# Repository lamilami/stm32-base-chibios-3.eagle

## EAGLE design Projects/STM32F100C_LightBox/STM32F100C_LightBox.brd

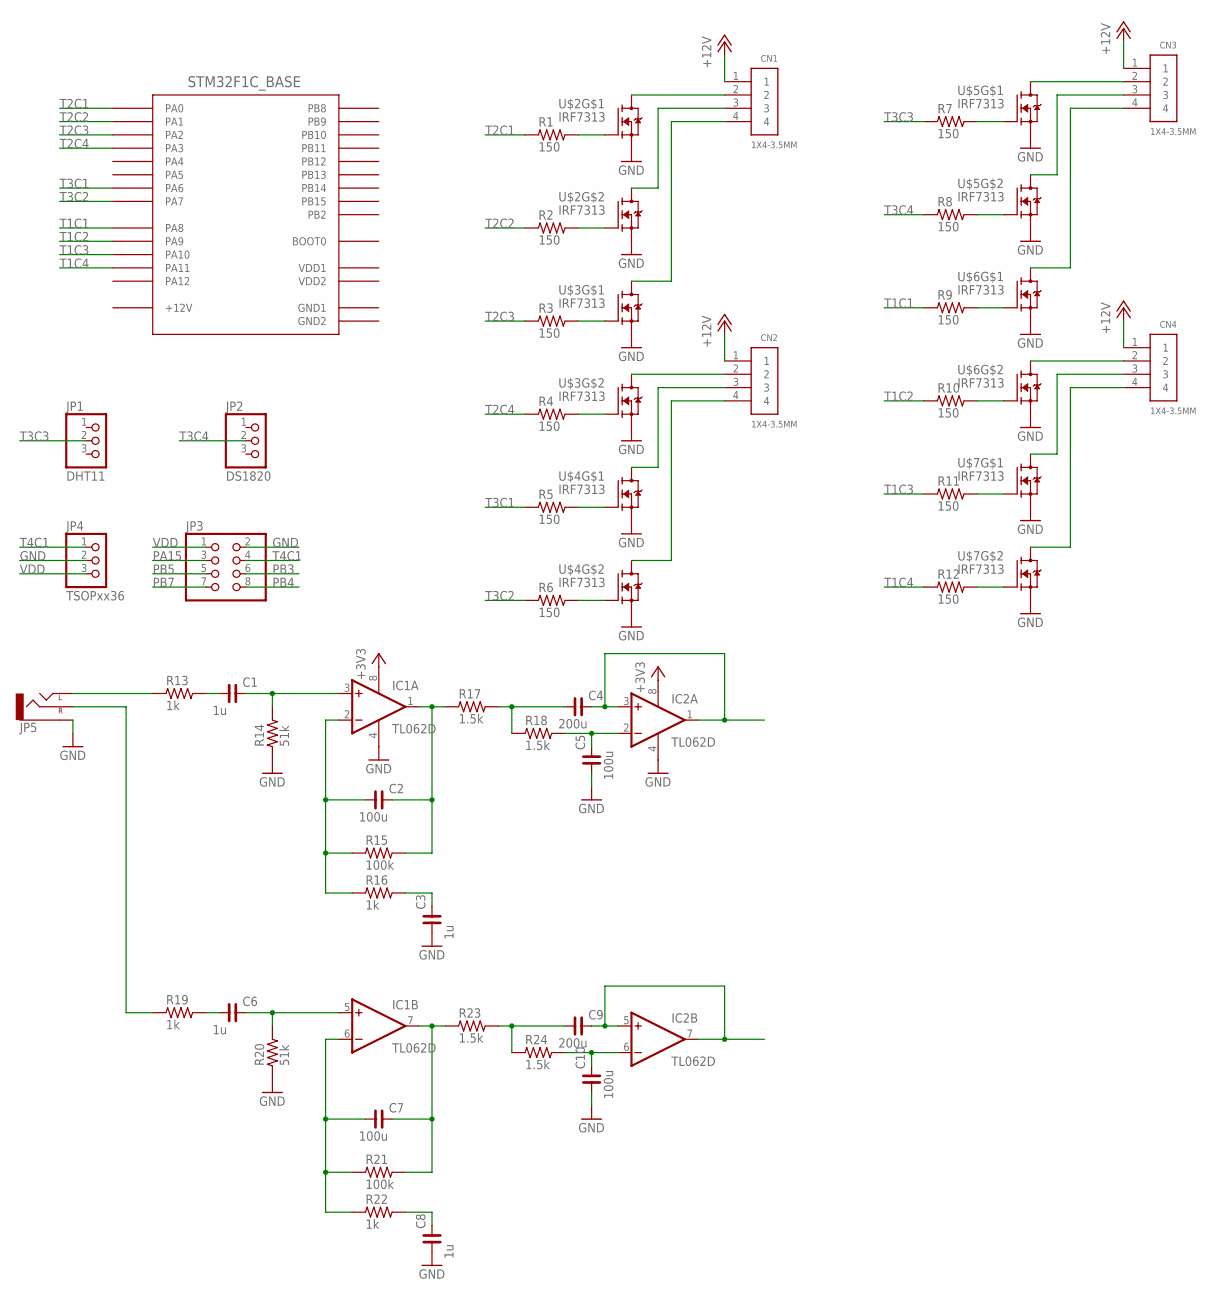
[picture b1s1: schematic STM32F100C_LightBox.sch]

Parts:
C1, C3, C6, C8: 1u; C0603
C2, C5, C7, C10: 100u; C0603
C4, C9: 200u; C0603
CN1, CN2, CN3, CN4: 1X4-3.5MM; 1X04-3.5MM
IC1, IC2: TL062D; SO08
JP1: DHT11; 1X03
JP2: DS1820; 1X03
JP3: PINHD-2X04_2.54; 2X04
JP4: TSOPxx36; 1X03
JP5: AUDIO-JACK; AUB-13
R1, R2, R3, R4, R5, R6, R7, R8, R9, R10, R11, R12: 150; R1206
R13, R16, R19, R22: 1k; R1206
R14, R20: 51k; R1206
R15, R21: 100k; R1206
R17, R18, R23, R24: 1.5k; R1206
U$1: STM32F1C_BASE; STM32F1_BASE
U$2, U$3, U$4, U$5, U$6, U$7: IRF7313; SO-8

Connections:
+3V3: IC1.8 (V+), IC2.8 (V+)
+12V: CN1.1, CN2.1, CN3.1, CN4.1, U$1.+12 (+12V)
GND: C3.1, C5.1, C8.1, C10.1, IC1.4 (V-), IC2.4 (V-), JP3.2, JP4.2, JP5.1 (SLEEVE), R14.1, R20.1, U$2.1 (S), U$2.3 (S), U$3.1 (S), U$3.3 (S), U$4.1 (S), U$4.3 (S), U$5.1 (S), U$5.3 (S), U$6.1 (S), U$6.3 (S), U$7.1 (S), U$7.3 (S)
unnamed: CN1.2, U$2.7 (D), U$2.8 (D)
unnamed: CN1.3, U$2.5 (D), U$2.6 (D)
unnamed: CN1.4, U$3.7 (D), U$3.8 (D)
unnamed: CN2.2, U$3.5 (D), U$3.6 (D)
unnamed: CN2.3, U$4.7 (D), U$4.8 (D)
unnamed: CN2.4, U$4.5 (D), U$4.6 (D)
unnamed: R1.2, U$2.2 (G)
unnamed: R2.2, U$2.4 (G)
unnamed: R3.2, U$3.2 (G)
unnamed: R4.2, U$3.4 (G)
unnamed: R5.2, U$4.2 (G)
unnamed: CN3.2, U$5.7 (D), U$5.8 (D)
unnamed: CN3.3, U$5.5 (D), U$5.6 (D)
unnamed: CN3.4, U$6.7 (D), U$6.8 (D)
unnamed: CN4.2, U$6.5 (D), U$6.6 (D)
unnamed: CN4.3, U$7.7 (D), U$7.8 (D)
unnamed: CN4.4, U$7.5 (D), U$7.6 (D)
unnamed: R7.2, U$5.2 (G)
unnamed: R8.2, U$5.4 (G)
unnamed: R9.2, U$6.2 (G)
unnamed: R10.2, U$6.4 (G)
unnamed: R11.2, U$7.2 (G)
unnamed: R6.2, U$4.4 (G)
unnamed: R12.2, U$7.4 (G)
unnamed: JP5.3 (LEFT), R13.1
unnamed: C1.1, R13.2
unnamed: C1.2, IC1.3 (+IN), R14.2
unnamed: C2.1, IC1.2 (-IN), R15.1, R16.1
unnamed: C2.2, IC1.1 (OUT), R15.2, R17.1
unnamed: C3.2, R16.2
unnamed: JP5.2 (RIGHT), R19.1
unnamed: C5.2, IC2.2 (-IN), R18.2
unnamed: C4.1, R17.2, R18.1
unnamed: C4.2, IC2.1 (OUT), IC2.3 (+IN)
unnamed: C6.1, R19.2
unnamed: C6.2, IC1.5 (+IN), R20.2
unnamed: C7.1, IC1.6 (-IN), R21.1, R22.1
unnamed: C7.2, IC1.7 (OUT), R21.2, R23.1
unnamed: C8.2, R22.2
unnamed: C9.1, R23.2, R24.1
unnamed: C10.2, IC2.6 (-IN), R24.2
unnamed: C9.2, IC2.5 (+IN), IC2.7 (OUT)
PA15: JP3.3
PB3: JP3.6
PB4: JP3.8
PB5: JP3.5
PB7: JP3.7
T1C1: R9.1, U$1.PA8
T1C2: R10.1, U$1.PA9
T1C3: R11.1, U$1.PA10
T1C4: R12.1, U$1.PA11
T2C1: R1.1, U$1.PA0
T2C2: R2.1, U$1.PA1
T2C3: R3.1, U$1.PA2
T2C4: R4.1, U$1.PA3
T3C1: R5.1, U$1.PA6
T3C2: R6.1, U$1.PA7
T3C3: JP1.2, R7.1
T3C4: JP2.2, R8.1
T4C1: JP3.4, JP4.1
VDD: JP3.1, JP4.3

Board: 2 copper layers, 52 parts (0 on the bottom side), 59 nets, no tracks yet.

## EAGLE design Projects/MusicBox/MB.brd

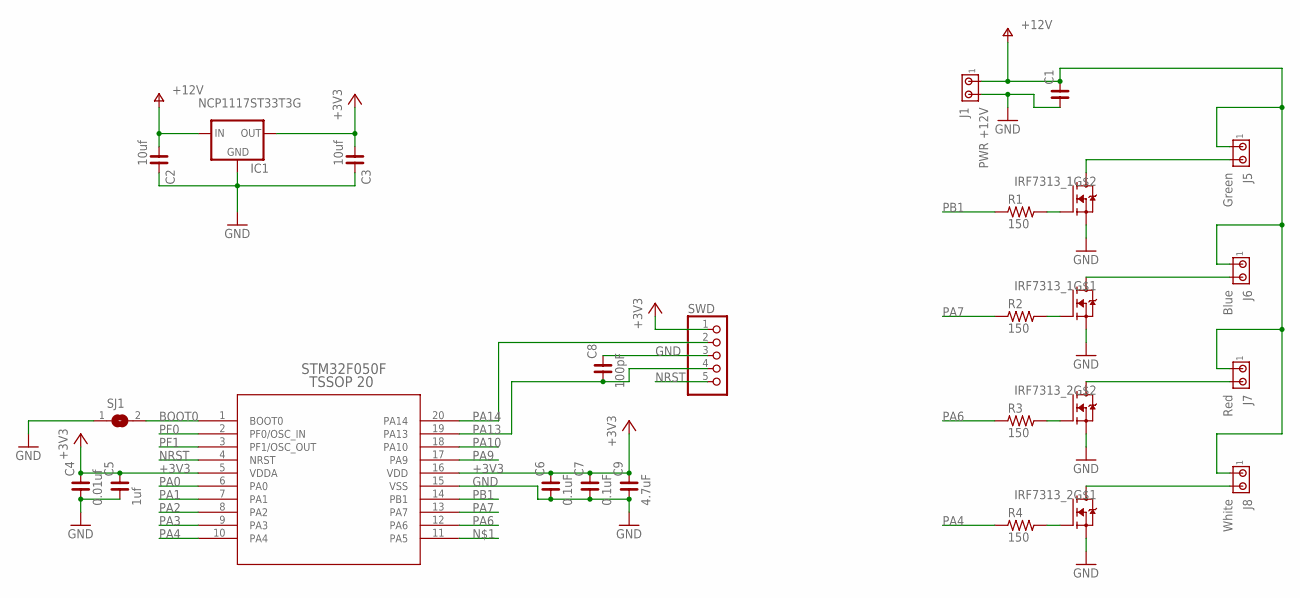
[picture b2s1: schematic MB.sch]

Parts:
C1: C_1206; C1206
C2, C3: 10uf; C1206
C4: 0.01uf; C1206
C5: 1uf; C1206
C6, C7: 0.1uF; C1206
C8: 100pF; C1206
C9: 4.7uF; C1206
IC1: NCP1117ST33T3G; SOT223
IRF7313_1, IRF7313_2: IRF7313; SO-8
J1: PWR +12V; 10X02MTA
J5: Green; 10X02MTA
J6: Blue; 10X02MTA
J7: Red; 10X02MTA
J8: White; 10X02MTA
R1, R2, R3, R4: 150; R1206
SJ1: SJ
SWD: PINHD-1X05_2.54-90°-S; 1X05/90-S
U$4: STM32F050F4P6; TSSOP20

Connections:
+3V3: C3.1, C4.2, C5.2, C6.2, C7.2, C9.2, IC1.2 (OUT), SWD.1, U$4.5 (VDDA), U$4.16 (VDD)
BOOT0: SJ1.2, U$4.1 (BOOT0)
GND: C1.1, C2.2, C3.2, C4.1, C5.1, C6.1, C7.1, C8.2, C9.1, IC1.1 (GND), IRF7313_1.1 (S), IRF7313_1.3 (S), IRF7313_2.1 (S), IRF7313_2.3 (S), J1.2, SJ1.1, SWD.3, U$4.15 (VSS)
unnamed: IRF7313_1.5 (D), IRF7313_1.6 (D), J5.2
unnamed: IRF7313_1.4 (G), R1.2
unnamed: IRF7313_1.2 (G), R2.2
unnamed: IRF7313_2.2 (G), R4.2
unnamed: IRF7313_2.4 (G), R3.2
unnamed: IRF7313_1.7 (D), IRF7313_1.8 (D), J6.2
unnamed: IRF7313_2.5 (D), IRF7313_2.6 (D), J7.2
unnamed: IRF7313_2.7 (D), IRF7313_2.8 (D), J8.2
NRST: SWD.5, U$4.4 (NRST)
PA0: U$4.6 (PA0)
PA1: U$4.7 (PA1)
PA2: U$4.8 (PA2)
PA3: U$4.9 (PA3)
PA4: R4.1, U$4.10 (PA4)
PA6: R3.1, U$4.12 (PA6)
PA7: R2.1, U$4.13 (PA7)
PA9: U$4.17 (PA9)
PA10: U$4.18 (PA10)
PA13: C8.1, SWD.4, U$4.19 (PA13)
PA14: SWD.2, U$4.20 (PA14)
PB1: R1.1, U$4.14 (PB1)
PF0: U$4.2 (PF0/OSC_IN)
PF1: U$4.3 (PF1/OSC_OUT)
V+: C1.2, C2.1, IC1.3 (IN), J1.1, J5.1, J6.1, J7.1, J8.1

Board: 2 copper layers, 24 parts (0 on the bottom side), 19 nets, no tracks yet.

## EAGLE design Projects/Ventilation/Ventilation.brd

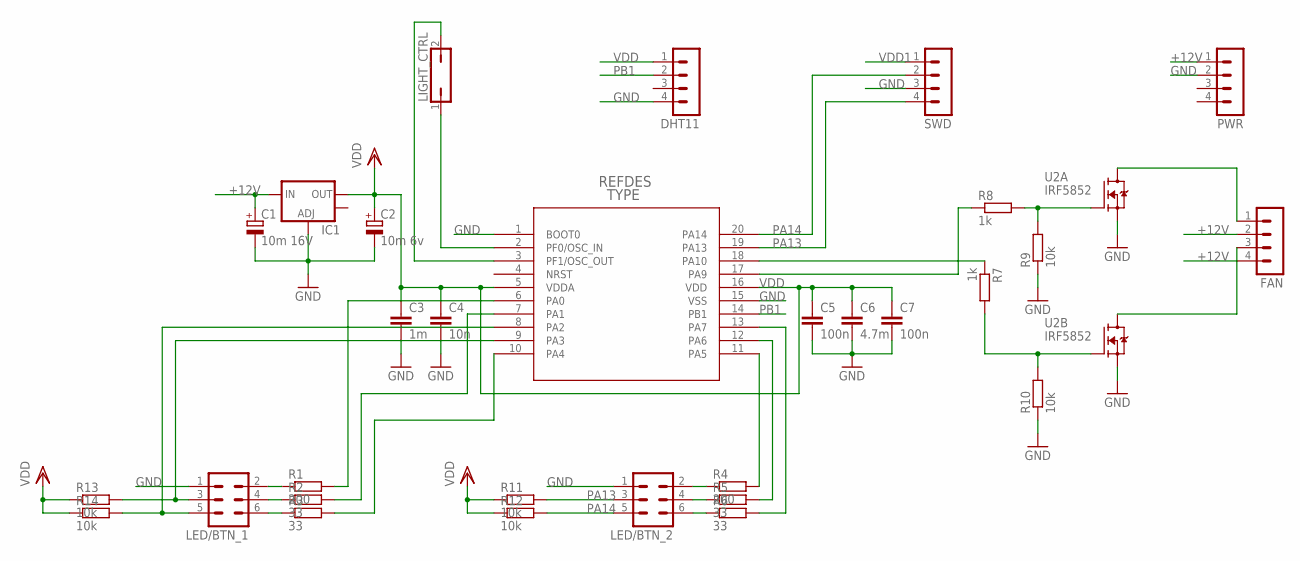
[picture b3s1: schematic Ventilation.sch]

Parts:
C1: 10m 16V; SMC_A
C2: 10m 6v; SMC_A
C3: 1m; C1206
C4: 10n; C1206
C5, C7: 100n; C1206
C6: 4.7m; C1206
DHT11: MA04-1
FAN: MA04-1
IC1: V_REG_LM1117SOT223; SOT223
LED/BTN_1, LED/BTN_2: MA03-2
LIGHT_CTRL: JP1Q; JP1
PWR: MA04-1
R1, R4: 200; R1206
R2, R3, R5, R6: 33; R1206
R7, R8: 1k; R1206
R9, R10, R11, R12, R13, R14: 10k; R1206
SWD: MA04-1
U2: IRF5852; SOT23-6
U$1: STM32F050F4P6; TSSOP20

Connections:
+12V: C1.+, FAN.2, FAN.4, IC1.3 (IN), PWR.1
GND: C1.-, C2.-, C3.2, C4.2, C5.2, C6.2, C7.2, DHT11.4, IC1.1 (ADJ), LED/BTN_1.1, LED/BTN_2.1, PWR.2, R9.1, R10.1, SWD.3, U2.2 (S), U2.5 (S), U$1.1 (BOOT0), U$1.15 (VSS)
unnamed: R8.1, U$1.17 (PA9)
unnamed: R7.2, R10.2, U2.3 (G)
unnamed: FAN.1, U2.6 (D)
unnamed: FAN.3, U2.4 (D)
unnamed: R7.1, U$1.18 (PA10)
unnamed: R8.2, R9.2, U2.1 (G)
unnamed: R1.2, U$1.6 (PA0)
unnamed: LIGHT_CTRL.1, U$1.2 (PF0/OSC_IN)
unnamed: LIGHT_CTRL.2, U$1.3 (PF1/OSC_OUT)
unnamed: R2.2, U$1.7 (PA1)
unnamed: LED/BTN_1.3, R13.2, U$1.9 (PA3)
unnamed: LED/BTN_1.5, R14.2, U$1.8 (PA2)
unnamed: LED/BTN_2.2, R4.1
unnamed: LED/BTN_2.4, R5.1
unnamed: LED/BTN_2.6, R6.1
unnamed: LED/BTN_1.2, R1.1
unnamed: LED/BTN_1.4, R2.1
unnamed: LED/BTN_1.6, R3.1
unnamed: R5.2, U$1.12 (PA6)
unnamed: R6.2, U$1.13 (PA7)
unnamed: R4.2, U$1.11 (PA5)
unnamed: R3.2, U$1.10 (PA4)
PA13: LED/BTN_2.3, R11.2, SWD.4, U$1.19 (PA13)
PA14: LED/BTN_2.5, R12.2, SWD.2, U$1.20 (PA14)
PB1: DHT11.2, U$1.14 (PB1)
VDD: C2.+, C3.1, C4.1, C5.1, C6.1, C7.1, DHT11.1, IC1.2 (OUT), R11.1, R12.1, R13.1, R14.1, U$1.5 (VDDA), U$1.16 (VDD)
VDD1: SWD.1

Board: 2 copper layers, 31 parts (0 on the bottom side), 28 nets, no tracks yet.

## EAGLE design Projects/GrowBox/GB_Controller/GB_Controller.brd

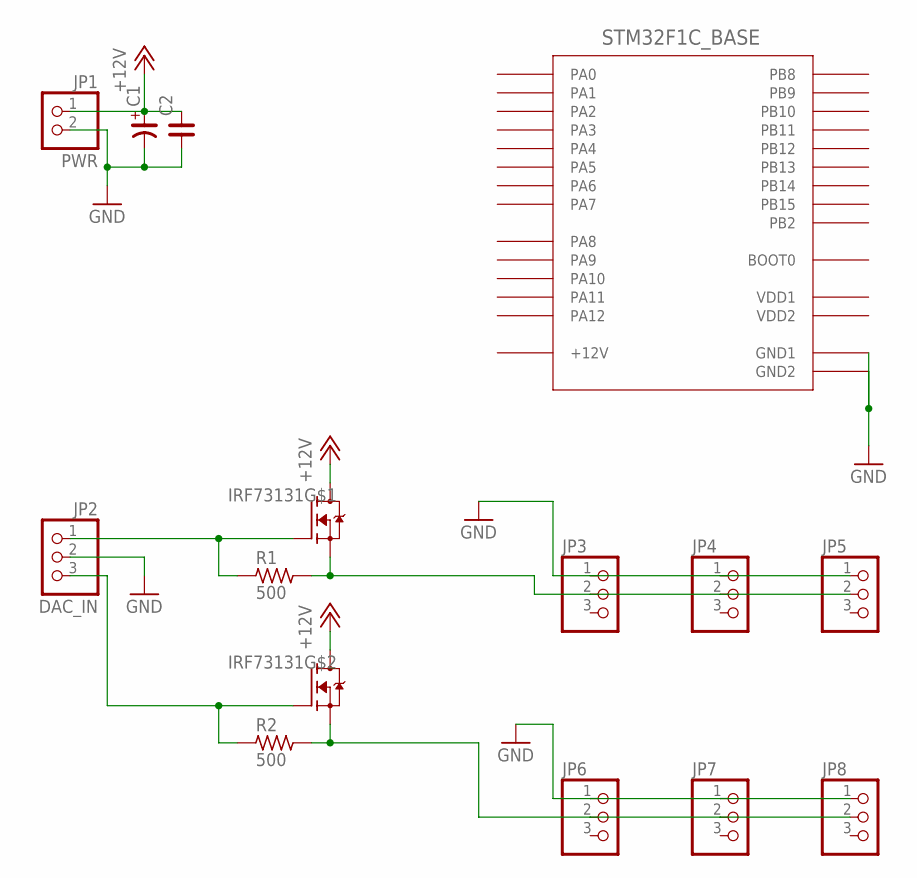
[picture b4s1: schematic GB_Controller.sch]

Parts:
C1: CP_7343; C7343/T
C2: C_0603; C0603
IRF73131: IRF7313; SO-8
JP1: PWR; 1X02-S
JP2: DAC_IN; 1X03-S
JP3, JP4, JP5, JP6, JP7, JP8: PINHD-1X03_2.54-S; 1X03-S
R1, R2: 500; R1206
STM32F1C_BASE1: STM32F1C_BASE; STM32F1_BASE

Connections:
+12V: C1.+, C2.2, IRF73131.5 (D), IRF73131.6 (D), IRF73131.7 (D), IRF73131.8 (D), JP1.1, STM32F1C_BASE1.+12 (+12V)
GND: C1.-, C2.1, JP1.2, JP2.2, JP3.1, JP4.1, JP5.1, JP6.1, JP7.1, JP8.1, STM32F1C_BASE1.GND (GND1), STM32F1C_BASE1.GND1 (GND2)
unnamed: IRF73131.1 (S), JP3.2, JP4.2, JP5.2, R1.2
unnamed: IRF73131.4 (G), JP2.3, R2.1
unnamed: IRF73131.2 (G), JP2.1, R1.1
unnamed: IRF73131.3 (S), JP6.2, JP7.2, JP8.2, R2.2

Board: 2 copper layers, 14 parts (0 on the bottom side), 6 nets, no tracks yet.

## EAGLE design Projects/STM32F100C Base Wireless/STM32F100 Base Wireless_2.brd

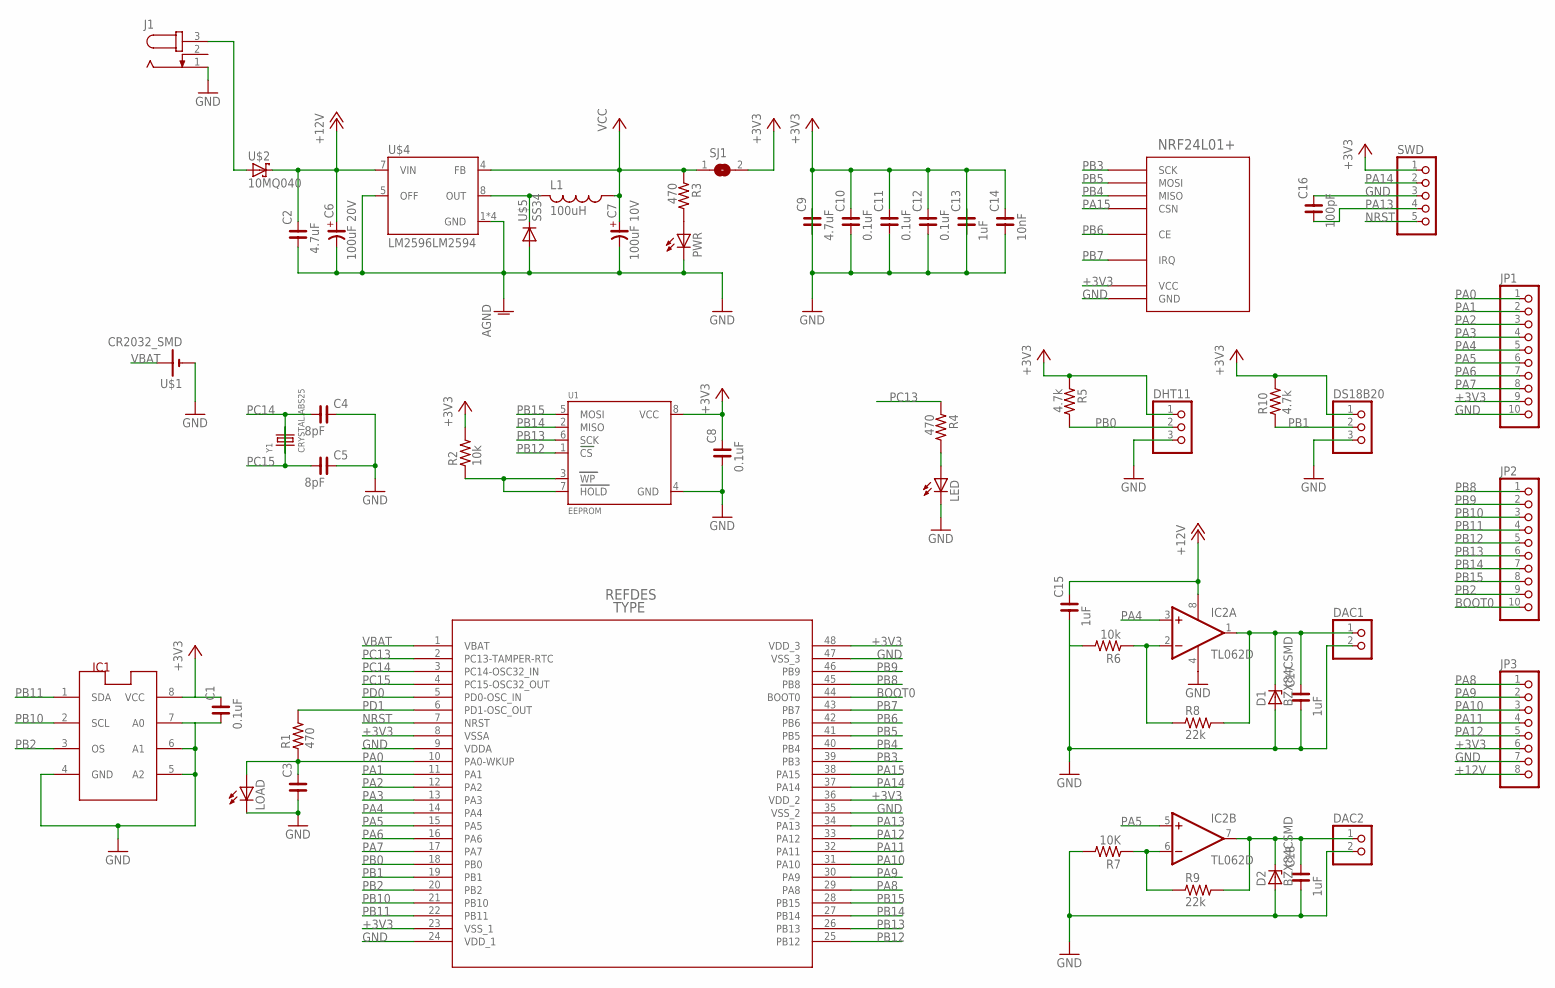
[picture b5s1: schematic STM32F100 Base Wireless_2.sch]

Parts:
C1, C8, C10, C11, C12: 0.1uF; C0603
C2, C9: 4.7uF; C0603
C3: C_0603; C0603
C4, C5: 8pF; C0603
C6: 100uF 20V; C7343/T
C7: 100uF 10V; C6032-28/T
C13, C15, C17, C18: 1uF; C0603
C14: 10nF; C0603
C16: 100pF; C0603
D1, D2: BZX84CSMD; TO236
DAC1, DAC2: PINHD-1X02_2.54-S; 1X02-S
DHT11: PINHD-1X03_2.54-S; 1X03-S
DS18B20: PINHD-1X03_2.54-S; 1X03-S
IC1: LM75_ICN; SO8_LM75
IC2: TL062D; SO08
J1: JACK-PLUG0; SPC4077
JP1, JP2: PINHD-1X10_2.54-S; 1X10-S
JP3: PINHD-1X08_2.54-S; 1X08-S
L1: 100uH; POWER-CHOKE_WE-TPC
LED: LEDCHIPLED_1206; CHIPLED_1206
LOAD: LEDCHIPLED_1206; CHIPLED_1206
PWR: LEDCHIPLED_1206; CHIPLED_1206
R1, R3, R4: 470; R1206
R2, R6: 10k; R1206
R5, R10: 4.7k; R1206
R7: 10K; R1206
R8, R9: 22k; R1206
SJ1: SJ
SWD: PINHD-1X05_2.54-90°-S; 1X05/90-S
U1: EEPROM; SOIC8_150MIL
U$1: CR2032_SMD; SMD_BH-2
U$2: 10MQ040; SMA
U$3: STM32F100C8T6B; LQFP-48
U$4: LM2596LM2594; SOIC8_150MIL
U$5: SS34; DO214AC
U$6: NRF24L01+
Y1: CRYSTAL.ABS25; ABS25

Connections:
+3V3: C1.2, C8.2, C9.1, C10.2, C11.2, C12.2, C13.1, C14.2, DHT11.1, DS18B20.1, IC1.8 (VCC), JP1.9, JP3.6, R2.2, R5.1, R10.2, SJ1.2, SWD.1, U1.8 (VCC), U$3.8 (VSSA), U$3.23 (VSS_1), U$3.36 (VDD_2), U$3.48 (VDD_3), U$6.VCC
+12V: C2.2, C6.+, C15.2, IC2.8 (V+), JP3.8, U$2.C, U$4.7 (VIN)
BOOT0: JP2.10, U$3.44 (BOOT0)
GND: C1.1, C2.1, C3.1, C4.2, C5.2, C6.-, C7.-, C8.1, C9.2, C10.1, C11.1, C12.1, C13.2, C14.1, C15.1, C16.2, C17.1, C18.1, D1.A, D2.A, DAC1.2, DAC2.2, DHT11.3, DS18B20.3, IC1.4 (GND), IC1.5 (A2), IC1.6 (A1), IC1.7 (A0), IC2.4 (V-), J1.1, JP1.10, JP3.7, LED.C, LOAD.C, PWR.C, R6.2, R7.2, SWD.3, U1.4 (GND), U$1.P$NEG (-), U$3.9 (VDDA), U$3.24 (VDD_1), U$3.35 (VSS_2), U$3.47 (VSS_3), U$4.1 (GND), U$4.2 (GND), U$4.3 (GND), U$4.5 (OFF), U$4.6 (GND), U$5.A, U$6.GND
IN_12V: J1.3, U$2.A
LM_OUT: L1.2, U$4.8 (OUT), U$5.C
LM_VCC: C7.+, L1.1, R3.1, SJ1.1, U$4.4 (FB)
unnamed: C17.2, D1.C, DAC1.1, IC2.1 (OUT), R8.2
unnamed: PWR.A, R3.2
unnamed: IC2.2 (-IN), R6.1, R8.1
unnamed: IC2.6 (-IN), R7.1, R9.1
unnamed: C18.2, D2.C, DAC2.1, IC2.7 (OUT), R9.2
unnamed: LED.A, R4.2
unnamed: R2.1, U1.3 (WP), U1.7 (HOLD)
NRST: SWD.5, U$3.7 (NRST)
PA0: C3.2, JP1.1, LOAD.A, R1.1, U$3.10 (PA0-WKUP)
PA1: JP1.2, U$3.11 (PA1)
PA2: JP1.3, U$3.12 (PA2)
PA3: JP1.4, U$3.13 (PA3)
PA4: IC2.3 (+IN), JP1.5, U$3.14 (PA4)
PA5: IC2.5 (+IN), JP1.6, U$3.15 (PA5)
PA6: JP1.7, U$3.16 (PA6)
PA7: JP1.8, U$3.17 (PA7)
PA8: JP3.1, U$3.29 (PA8)
PA9: JP3.2, U$3.30 (PA9)
PA10: JP3.3, U$3.31 (PA10)
PA11: JP3.4, U$3.32 (PA11)
PA12: JP3.5, U$3.33 (PA12)
PA13: C16.1, SWD.4, U$3.34 (PA13)
PA14: SWD.2, U$3.37 (PA14)
PA15: U$3.38 (PA15), U$6.CSN
PB0: DHT11.2, R5.2, U$3.18 (PB0)
PB1: DS18B20.2, R10.1, U$3.19 (PB1)
PB2: IC1.3 (OS), JP2.9, U$3.20 (PB2)
PB3: U$3.39 (PB3), U$6.SCK
PB4: U$3.40 (PB4), U$6.MISO
PB5: U$3.41 (PB5), U$6.MOSI
PB6: U$3.42 (PB6), U$6.CE
PB7: U$3.43 (PB7), U$6.IRQ
PB8: JP2.1, U$3.45 (PB8)
PB9: JP2.2, U$3.46 (PB9)
PB10: IC1.2 (SCL), JP2.3, U$3.21 (PB10)
PB11: IC1.1 (SDA), JP2.4, U$3.22 (PB11)
PB12: JP2.5, U1.1 (CS), U$3.25 (PB12)
PB13: JP2.6, U1.6 (SCK), U$3.26 (PB13)
PB14: JP2.7, U1.2 (MISO), U$3.27 (PB14)
PB15: JP2.8, U1.5 (MOSI), U$3.28 (PB15)
PC13: R4.1, U$3.2 (PC13-TAMPER-RTC)
PC14: C4.1, U$3.3 (PC14-OSC32_IN), Y1.1
PC15: C5.1, U$3.4 (PC15-OSC32_OUT), Y1.4 (2)
PD0: U$3.5 (PD0-OSC_IN)
PD1: R1.2, U$3.6 (PD1-OSC_OUT)
VBAT: U$1.P$POS1 (+), U$3.1 (VBAT)

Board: 2 copper layers, 54 parts (5 on the bottom side), 52 nets, no tracks yet.

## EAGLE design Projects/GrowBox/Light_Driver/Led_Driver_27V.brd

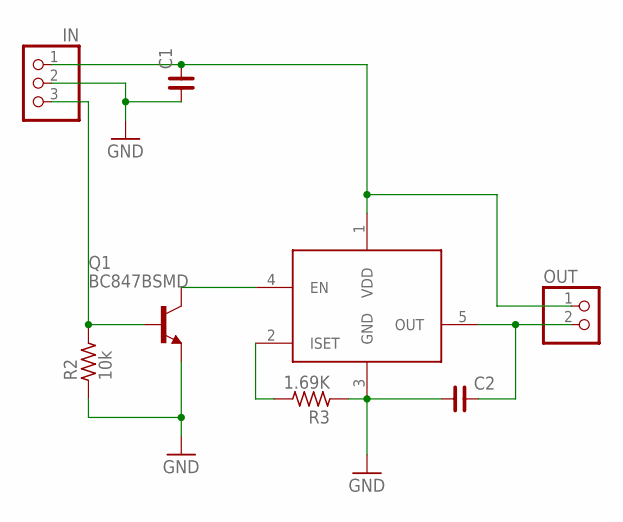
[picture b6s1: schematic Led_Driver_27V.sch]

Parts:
C1, C2: C_0603; C0603
IN: PINHD-1X03_2.54-S; 1X03-S
OUT: PINHD-1X02_2.54-S; 1X02-S
Q1: BC847BSMD; SOT23
R2: 10k; R1206
R3: 1.69K; R1206
U$1: AMC7140; TO252-5L

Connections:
GND: C1.1, C2.1, IN.2, Q1.2 (E), R2.1, R3.1, U$1.3 (GND)
unnamed: C2.2, OUT.2, U$1.5 (OUT)
unnamed: Q1.3 (C), U$1.4 (EN)
unnamed: R3.2, U$1.2 (ISET)
unnamed: IN.3, Q1.1 (B), R2.2
VDD: C1.2, IN.1, OUT.1, U$1.1 (VDD)

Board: 2 copper layers, 8 parts (0 on the bottom side), 6 nets, no tracks yet.

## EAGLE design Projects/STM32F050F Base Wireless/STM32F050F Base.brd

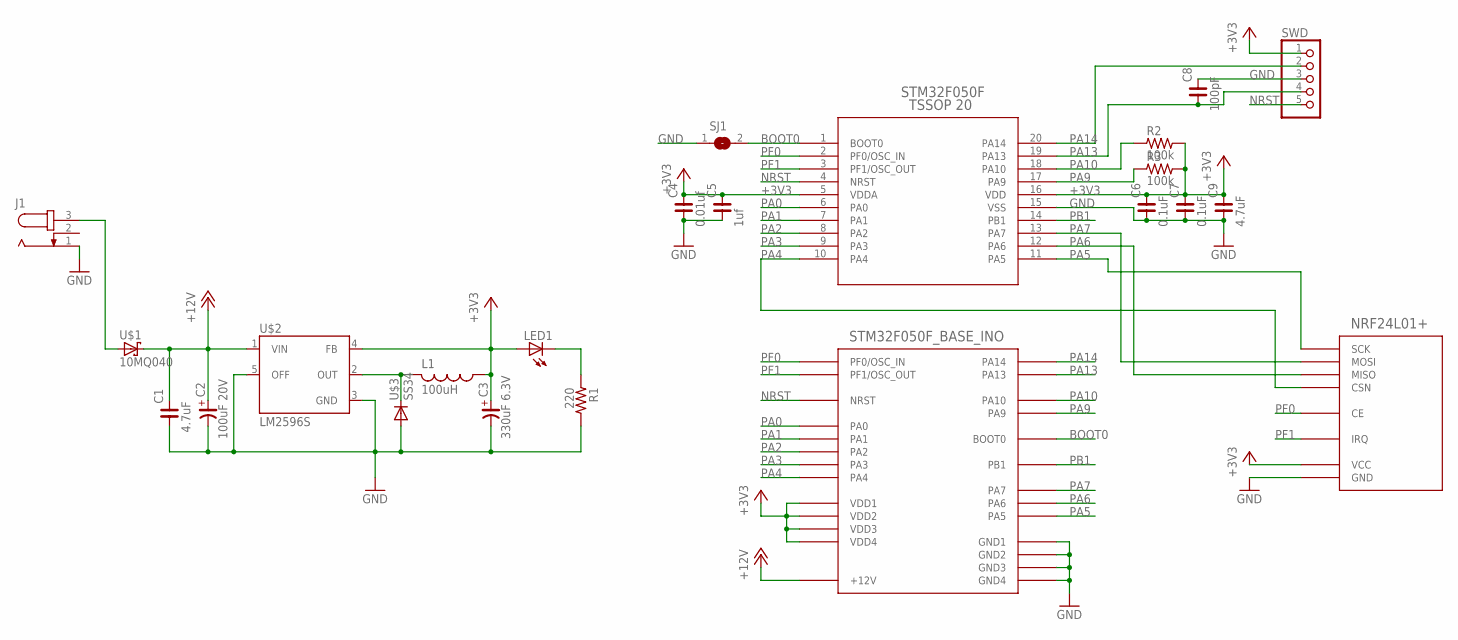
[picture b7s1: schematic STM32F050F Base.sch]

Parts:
C1, C9: 4.7uF; C1206
C2: 100uF 20V; C7343/T
C3: 330uF 6.3V; C7343/T
C4: 0.01uf; C1206
C5: 1uf; C1206
C6, C7: 0.1uF; C1206
C8: 100pF; C1206
J1: JACK-PLUG0; SPC4077
L1: 100uH; POWER-CHOKE_WE-TPC
LED1: LEDCHIPLED_1206; CHIPLED_1206
R1: 220; R1206
R2, R3: 100k; R1206
SJ1: SJ
SWD: PINHD-1X05_2.54-90°-S; 1X05/90-S
U$1: 10MQ040; SMA
U$2: LM2596S; TO263-5
U$3: SS34; SMC
U$4: STM32F050F4P6; TSSOP20
U$5: STM32F050F_BASE_INO; STM32_BASE_INO
U$6: NRF24L01+

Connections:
+3V3: C3.+, C4.2, C5.2, C6.2, C7.2, C9.2, L1.1, LED1.A, R2.2, R3.2, SWD.1, U$2.4 (FB), U$4.5 (VDDA), U$4.16 (VDD), U$5.VDD1, U$5.VDD2, U$5.VDD3, U$5.VDD4, U$6.VCC
+12V: C1.2, C2.+, U$1.C, U$2.1 (VIN), U$5.+12V
BOOT0: SJ1.2, U$4.1 (BOOT0), U$5.BOOT0
GND: C1.1, C2.-, C3.-, C4.1, C5.1, C6.1, C7.1, C8.2, C9.1, J1.1, R1.2, SJ1.1, SWD.3, U$2.3 (GND), U$2.5 (OFF), U$3.A, U$4.15 (VSS), U$5.GND1, U$5.GND2, U$5.GND3, U$5.GND4, U$6.GND
unnamed: LED1.C, R1.1
unnamed: J1.3, U$1.A
unnamed: L1.2, U$2.2 (OUT), U$3.C
NRST: SWD.5, U$4.4 (NRST), U$5.NRST
PA0: U$4.6 (PA0), U$5.PA0
PA1: U$4.7 (PA1), U$5.PA1
PA2: U$4.8 (PA2), U$5.PA2
PA3: U$4.9 (PA3), U$5.PA3
PA4: U$4.10 (PA4), U$5.PA4, U$6.CSN
PA5: U$4.11 (PA5), U$5.PA5, U$6.SCK
PA6: U$4.12 (PA6), U$5.PA6, U$6.MISO
PA7: U$4.13 (PA7), U$5.PA7, U$6.MOSI
PA9: R3.1, U$4.17 (PA9), U$5.PA9
PA10: R2.1, U$4.18 (PA10), U$5.PA10
PA13: C8.1, SWD.4, U$4.19 (PA13), U$5.PA13
PA14: SWD.2, U$4.20 (PA14), U$5.PA14
PB1: U$4.14 (PB1), U$5.PB1
PF0: U$4.2 (PF0/OSC_IN), U$5.PF0 (PF0/OSC_IN), U$6.CE
PF1: U$4.3 (PF1/OSC_OUT), U$5.PF1 (PF1/OSC_OUT), U$6.IRQ

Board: 2 copper layers, 23 parts (3 on the bottom side), 23 nets, no tracks yet.

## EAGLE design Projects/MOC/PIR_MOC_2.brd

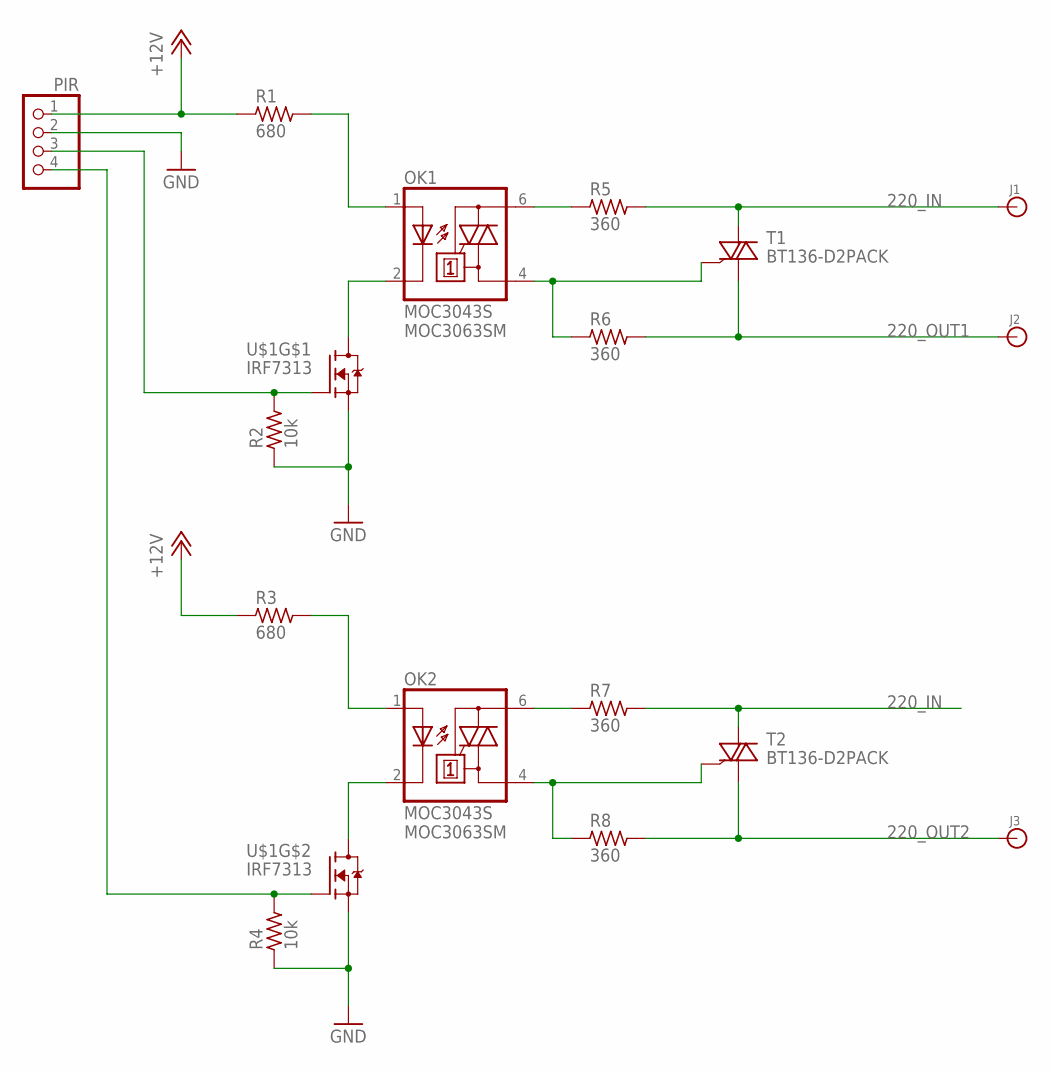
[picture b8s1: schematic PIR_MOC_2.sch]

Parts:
J1, J2, J3: BANANA_CONN
OK1, OK2: MOC3043S; DIL6-SMD; MPN MOC3063SM
PIR: PINHD-1X04_2.54-S; 1X04-S
R1, R3: 680; R1206
R2, R4: 10k; R1206
R5, R6, R7, R8: 360; R1206
T1, T2: BT136-D2PACK; TO263
U$1: IRF7313; SO-8

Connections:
220_IN: J1.P$1, R5.2, R7.2, T1.3 (A2), T2.3 (A2)
220_MOC_AC: OK1.6 (A2), R5.1
220_MOC_AC1: OK2.6 (A2), R7.1
220_MOC_N: OK1.4 (A1), R6.1, T1.2 (G)
220_MOC_N1: OK2.4 (A1), R8.1, T2.2 (G)
220_OUT1: J2.P$1, R6.2, T1.1 (A1)
220_OUT2: J3.P$1, R8.2, T2.1 (A1)
+12V: PIR.1, R1.1, R3.1
GND: PIR.2, R2.1, R4.1, U$1.1 (S), U$1.3 (S)
unnamed: OK2.2 (C), U$1.5 (D), U$1.6 (D)
unnamed: OK2.1 (A), R3.2
unnamed: PIR.4, R4.2, U$1.4 (G)
unnamed: OK1.2 (C), U$1.7 (D), U$1.8 (D)
unnamed: OK1.1 (A), R1.2
unnamed: PIR.3, R2.2, U$1.2 (G)

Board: 2 copper layers, 17 parts (6 on the bottom side), 15 nets, no tracks yet.

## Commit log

2015-01-20 hgignore update...
2015-01-20 Added home projects...
2015-01-20 Test update...
2015-01-21 Added libraries from work...
2015-01-21 Added projects from work...
2015-01-21 Some cleanup...
2015-01-21 LiteBox Project started...
2015-01-24 LiteBox Project update...
2015-02-02 LB Audio in...

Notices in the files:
parts and their libraries:
rc-master-smd: Copyright (C) 2007, Bob Starr
SparkFun-PowerIC: Licensing: CC v3.0 Share-Alike You are welcome to use this library for commercial purposes.
